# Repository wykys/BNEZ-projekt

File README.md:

# Projekt BNEZ zdroj dvou napětí

Uin = 18V ÷ 32V
Uout1 = 9V 2,4A
Uout2 = 4,5V 0,5A

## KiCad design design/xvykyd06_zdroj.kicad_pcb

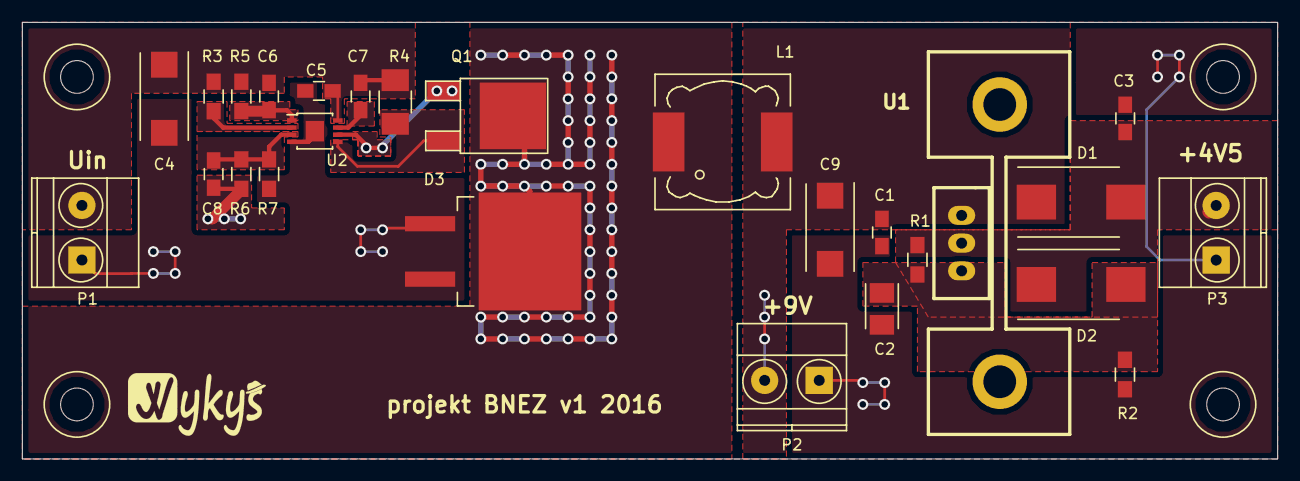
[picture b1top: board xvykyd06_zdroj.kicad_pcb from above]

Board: 2 copper layers, 115.0 x 40.0 mm, 30 parts (0 on the bottom side), 12 nets.

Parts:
C1: 100n; C_0805_HandSoldering
C2: 10u/20V; TantalC_SizeB_EIA-3528_Reflow
C3, C5: 1u; C_0805_HandSoldering
C4: 10u/50V; TantalC_SizeD_EIA-7343_Reflow
C6: 1n; C_0805_HandSoldering
C7: 470n; C_0805_HandSoldering
C8: 6n8; C_0805_HandSoldering
C9: 68u/20V; TantalC_SizeD_EIA-7343_Reflow
D1, D2: BYG10D-E3/TR; DO-214AB_Handsoldering
D3: STPS20M100S; TO-263-3Lead
L1: 47u; Choke_SMD_12x12mm_h6mm
M1, M2, M3, M4: M3
P1: PWR IN; TerminalBlock_Pheonix_MKDS1.5-2pol
P2: +9V; TerminalBlock_Pheonix_MKDS1.5-2pol
P3: +4V5; TerminalBlock_Pheonix_MKDS1.5-2pol
Q1: FDD5614P; TO-252-2Lead
R1: 510R; R_0805_HandSoldering
R2: 1k3; R_0805_HandSoldering
R3: 180k; R_0805_HandSoldering
R4: R01; R_1210_HandSoldering
R5: 1k5; R_0805_HandSoldering
R6: 6k2; R_0805_HandSoldering
R7: 1k; R_0805_HandSoldering
U1: LM317KCS; to220_std_11cw
U2: LM25085MYE; MSOP-8-1EP_3x3mm_Pitch0.65mm

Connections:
+4V5: C3.1, D1.2, D2.1, P3.2, R1.1, U1.2
+9V: C1.1, C8.1, C9.1, D1.1, L1.2, P2.1, R6.1, U1.3
GND: C1.2, C2.2, C3.2, C4.2, C5.2, C9.2, D3.2, P1.2, P2.2, P3.1, R2.2, R7.2, U2.4, U2.9
unnamed: C2.1, D2.2, R1.2, R2.1, U1.1
unnamed: C6.1, R5.2, U2.1
unnamed: C7.1, U2.7
unnamed: C8.2, R6.2, R7.1, U2.3
unnamed: D3.1, L1.1, Q1.2
unnamed: Q1.1, U2.6
unnamed: Q1.3, R4.2, U2.5
unnamed: R3.2, U2.2
VCC: C4.1, C5.1, C6.2, C7.2, P1.1, R3.1, R4.1, R5.1, U2.8

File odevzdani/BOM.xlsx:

ref | hodnota | footprint | cena | link | datasheet
C1 | 100n | 0805 | 1 | standatd 10%
C2 | 10u/20V | Tantal_SizeB | 12.451000000000001 | http://cz.farnell.com/kemet/t491b106k020at/cap-tant-10uf-20v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 | http://www.farnell.com/datasheets/2121504.pdf
C3 | 1u | 0805 | 20 | standatd 10%
C4 | 10u/50V | Tantal_SizeD | 62.392000000000003 | http://cz.farnell.com/kemet/t491d106k050at/cap-tant-10uf-50v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 | http://www.farnell.com/datasheets/2122222.pdf
C5 | 1u | 0805 | 20 | standatd 10%
C6 | 1n | 0805 | 1 | standatd 10%
C7 | 470n | 0805 | 1 | standatd 10%
C8 | 6n8 | 0805 | 1 | standatd 10%
C9 | 68u/20V | Tantal_SizeD | 40.857999999999997 | http://cz.farnell.com/kemet/t491d686k020at/cap-tant-68uf-20v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 | http://www.farnell.com/datasheets/2121528.pdf
D1 | BYG10D-E3/TR | DO-214AC | 6.4320000000000004 | http://cz.farnell.com/vishay/byg10d-e3-tr/diode-standard-1-5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 | http://www.farnell.com/datasheets/2046084.pdf
D2 | BYG10D-E3/TR | DO-214AC | 6.4320000000000004 | http://cz.farnell.com/vishay/byg10d-e3-tr/diode-standard-1-5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 | http://www.farnell.com/datasheets/2046084.pdf
D3 | STPS20M100S | TO-263 | 64.876000000000005 | http://cz.farnell.com/stmicroelectronics/stps20m100sg-tr/dio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 | http://www.farnell.com/datasheets/1716357.pdf
L1 | 47u | Choke_SMD_12x12mm_h6mm | 57.423000000000002 | http://cz.farnell.com/bourns/srp1265a-470m/inductor-shielded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 | http://www.farnell.com/datasheets/2059704.pdf
P1 | MA522-500M02 | TerminalBlock_Pheonix_MKDS1.5-2pol | 7.0439999999999996 | http://cz.farnell.com/multicomp/ma522-500m02/terminal-block-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 | http://www.farnell.com/datasheets/2059704.pdf
P2 | MA522-500M02 | TerminalBlock_Pheonix_MKDS1.5-2pol | 7.0439999999999996 | http://cz.farnell.com/multicomp/ma522-500m02/terminal-block-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 | http://www.farnell.com/datasheets/1706879.pdf
P3 | MA522-500M02 | TerminalBlock_Pheonix_MKDS1.5-2pol | 7.0439999999999996 | http://cz.farnell.com/multicomp/ma522-500m02/terminal-block-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 | http://www.farnell.com/datasheets/1706879.pdf
Q1 | FDD5614P | TO-252 | 12.92 | http://cz.farnell.com/fairchild-semiconductor/fdd5614p/mosfe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 | http://www.farnell.com/datasheets/1706879.pdf
R1 | 510R | 0805 | 2 | standatd 1%
R2 | 1k3 | 0805 | 2 | standatd 1%
R3 | 180k | 0805 | 2 | standatd 1%
R4 | R01 | 1210 | 8 | standatd 1%
R5 | 1k5 | 0805 | 2 | standatd 1%
R6 | 6k2 | 0805 | 2 | standatd 1%
R7 | 1k | 0805 | 2 | standatd 1%
U1 | LM317KCS | TO-220 | 16.012 | http://cz.farnell.com/texas-instruments/lm317kcs/v-reg-37vin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 3to2… | http://www.farnell.com/datasheets/1994326.pdf
U2 | LM25085MYE | MSOP | 60.734999999999999 | http://cz.farnell.com/texas-instruments/lm25085mye/ic-sw-buc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 | http://cz.farnell.com/texas-instruments/lm25085mye/ic-sw-buc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
 | chladič | na TO-220 | 48.036000000000001 | http://cz.farnell.com/fischer-elektronik/sk-104-38-1-sts/hea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 | http://www.farnell.com/datasheets/1332085.pdf
Celková cena: |  |  | 473.69899999999996

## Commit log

2016-11-27 :octocat: Added .gitattributes
2016-11-27 Revert ":octocat: Added .gitattributes"
    This reverts commit 2eff052c4d8cdfe0702f181be18f45f1002f0ceb.
2016-11-27 1.0
    Nahrání souborů
2016-11-27 readme
2016-11-27 o projektu
